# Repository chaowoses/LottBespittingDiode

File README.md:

# Lott-Bespitting Diode (LBD)

A high-intensity IR blaster built on the RP2040. Browser-native control over WebSerial, MOSFET-driven IR output, 38kHz NEC modulation. Fully open source.

[Home Page](https://chaowoses.dev/LottBespittingDiode/) &middot; [Controller](https://chaowoses.dev/LottBespittingDiode/controller.html)

Named for Mrs. Lott, the worst teacher I ever had, and her classroom projector.

---

## Features

- **Web Controller**: Full single-page app to manage IR remotes, browse the Flipper-IRDB, compose NEC signals, and transmit over WebSerial
- **In-Browser Schematic Viewer**: Browse all hardware schematics directly on the landing page via KiCanvas
- **Auto-Generated BOM**: Bill of materials extracted from KiCad schematics and embedded in the landing page, updated on every push
- **IRDB Integration**: Browse and import from [Lucaslhm/Flipper-IRDB](https://github.com/Lucaslhm/Flipper-IRDB) directly from the controller
- **NEC Protocol Engine**: CircuitPython firmware with hardware-timed 38kHz carrier modulation
- **Library Management**: Organize remotes and signals in folders with drag-and-drop, favorites, and inline editing

---

## Project Structure

```
app/                  # Web front-end
  index.html          # Landing page (hero, BOM, schematic viewer, docs)
  controller.html     # WebSerial controller app
  landing/
    index.css         # Landing page styles (dark theme, purple/amber)
    index.js          # Landing page interactivity (tabs, viewer)
    insults.json      # Footer quotes
    three-scene.js    # Three.js particle background
  controller/
    style.css         # Controller styles
    scripts/
      app.js          # Init, event listeners, tab switching
      state.js        # State management, library CRUD, localStorage
      serial.js       # WebSerial connection, log bar
      transmit.js     # Hex input, NEC encoding, transmit history, save form
      library-ui.js   # Library pane, remote view, favorites, inline edits
      sidebar.js      # Sidebar toggle, resize, tree rendering
      modals.js       # Modal dialogs (folder, rename, delete, clear)
      drag-drop.js    # Drag-and-drop reordering in sidebar tree
      import.js       # .ir file parsing and import
      irdb.js         # Flipper-IRDB browsing and import
      utils.js        # escHtml, escAttr helpers

firmware/             # CircuitPython firmware
  code.py             # NEC protocol engine over USB serial
  lib/                # Runtime libraries

hardware/             # KiCad hardware design
  LBD.kicad_sch       # Main schematic (RP2040, MOSFET, IR matrix)
  power.kicad_sch     # Power regulation (TPSM828214SILR)
  flash.kicad_sch     # External flash (W25Q128)
  usb.kicad_sch       # USB-C (USB4155)
  infared.kicad_sch   # IR LED output stage
  LBD.kicad_pcb       # PCB layout
  LBD_Library/        # Custom KiCad symbols and footprints
  prototype/          # Breadboard/perfboard prototype variant
  reviews/            # Design reviews and schematic analysis outputs

scripts/              # Utility scripts
  generate_bom.py     # Auto-generates BOM HTML from KiCad schematics
  ir_tester.py        # Standalone IR transmission test
```

---

## Hardware

> The embedded PCB design isn't finalized yet. Build the prototype on a breadboard or perfboard using the [prototype schematic](hardware/prototype.kicad_sch).

The full design targets a custom PCB with an RP2040, MOSFET-switched IR LED array, USB-C, and external flash. Five KiCad schematics cover the main board, power regulation, flash memory, USB connector, and a simplified prototype variant.

---

## Firmware

The [CircuitPython firmware](firmware/code.py) implements a standard NEC protocol engine:

- 38kHz carrier modulation via `pulseio.PulseOut`
- Listens for 4-byte NEC arrays over USB serial
- Drives a status LED and the IR output on GPIO
- Header: 9000&micro;s mark / 4500&micro;s space
- Bit coding: 560&micro;s mark + 1690&micro;s (1) or 560&micro;s (0)
- Compatible with any NEC IR receiver

```python
import time
import board
import pwmio

# 38kHz carrier wave initialization
ir_pwm = pwmio.PWMOut(board.GP16, frequency=38000, duty_cycle=0)

def pulse_nec(mark_us, space_us):
    # Enable carrier wave modulation for duration of mark
    ir_pwm.duty_cycle = 32768  # 50% duty cycle
    time.sleep_us(mark_us)

    # Disable carrier wave modulation for duration of space
    ir_pwm.duty_cycle = 0
    time.sleep_us(space_us)
```

---

## Web Interface

Two pages are served via GitHub Pages:

| Page | Description |
|---|---|
| **Landing Page** (`index.html`) | Project overview, BOM table, KiCanvas schematic viewer, architecture docs, features, setup guide |
| **Controller** (`controller.html`) | Full WebSerial-based remote control app with library management, IRDB browser, signal composer, and transmit history |

---

## Setup & Flash

> Build the prototype on a breadboard or perfboard using the [prototype schematic](hardware/prototype.kicad_sch).

<details>
<summary><strong>DIY / Prototype Only</strong>: Steps 1 and 2 (skip if you have a pre-assembled unit)</summary>

### Step 1: Enter Bootloader Mode

Press and hold the **BOOT** button on the board, then connect it to your computer via a data-capable USB cable. Release the button once the drive mounts.

### Step 2: Install CircuitPython

A mass storage volume named `RPI-RP2` will appear. Drag and drop the appropriate CircuitPython `.uf2` payload onto its root directory. The board will automatically reboot and remount as `CIRCUITPY`.

</details>

### Step 3: Deploy Firmware

Copy the contents of `firmware/` onto the `CIRCUITPY` volume root:

- `code.py`
- `lib/`

### Step 4: Plug It In & Open the Controller

Keep the device connected via USB, then open the [web controller](https://chaowoses.dev/LottBespittingDiode/controller.html) in a Chromium-based browser. Click **Connect** to establish the WebSerial session.

To run locally (required for development):

```bash
git clone https://github.com/chaowoses/LottBespittingDiode.git
cd LottBespittingDiode
python -m http.server 8080
# open http://localhost:8080
```

---

## License & Terms of Use

> [!CAUTION]
> **STRICTLY PROHIBITED FOR ILLEGAL USE**
>
> This project is designed solely for personal engineering research, hardware prototyping, and authorized testing.
> You may only operate this device on equipment you personally own or have explicit permission to control.
> The creator assumes no liability for misuse, property disruption, or equipment damage.

This project (software, firmware, schematics, PCB layouts, and documentation) is licensed under the **GNU General Public License v3.0 (GPL-3.0)**.

Copyright &copy; 2026 Josh Felder (Chaos). All Rights Reserved.

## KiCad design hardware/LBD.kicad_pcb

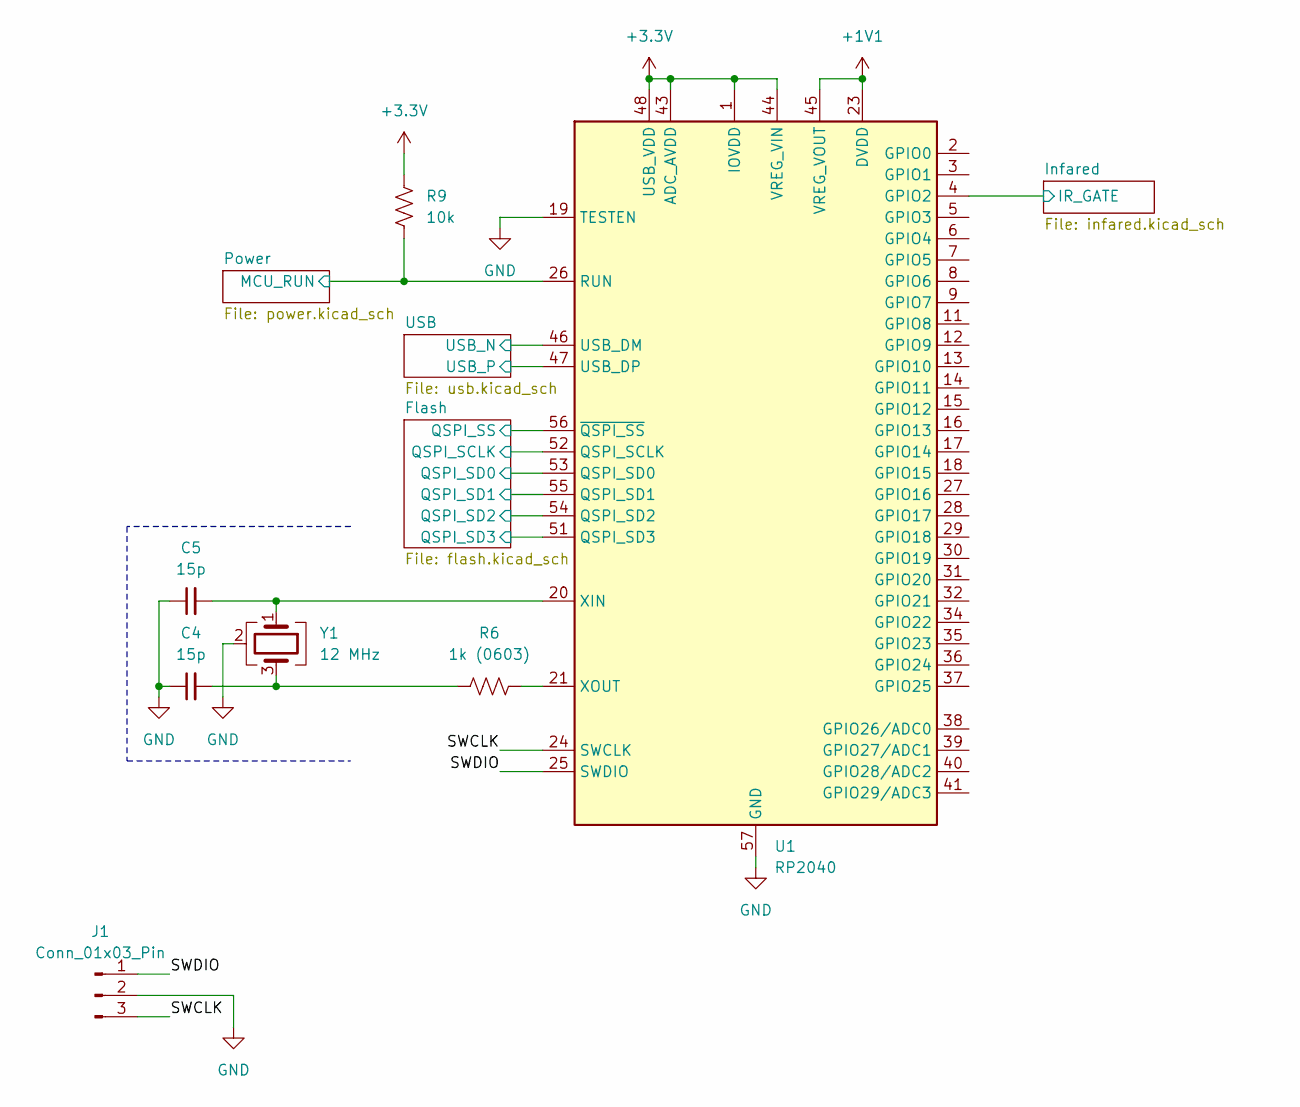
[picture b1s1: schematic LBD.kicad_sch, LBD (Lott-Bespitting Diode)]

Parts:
C4, C5: 15p; C_0201_0603Metric
J1: Conn_01x03_Pin; PinHeader_1x03_P2.54mm_Vertical_SMD_Pin1Left
R6: 1k (0603); R_0603_1608Metric
R9: 10k; R_0201_0603Metric
U1: RP2040; QFN-56-1EP_7x7mm_P0.4mm_EP3.2x3.2mm
Y1: 12 MHz

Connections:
+1V1: U1.23 (DVDD), U1.45 (VREG_VOUT), U1.50 (DVDD); also elsewhere on the board
+3.3V: R9.2, U1.1 (IOVDD), U1.10 (IOVDD), U1.22 (IOVDD), U1.33 (IOVDD), U1.42 (IOVDD), U1.43 (ADC_AVDD), U1.44 (VREG_VIN), U1.48 (USB_VDD), U1.49 (IOVDD); also elsewhere on the board
/Flash/QSPI_SCLK: U1.52 (QSPI_SCLK); also elsewhere on the board
/Flash/QSPI_SD0: U1.53 (QSPI_SD0); also elsewhere on the board
/Flash/QSPI_SD1: U1.55 (QSPI_SD1); also elsewhere on the board
/Flash/QSPI_SD2: U1.54 (QSPI_SD2); also elsewhere on the board
/Flash/QSPI_SD3: U1.51 (QSPI_SD3); also elsewhere on the board
/Flash/QSPI_SS: U1.56 (~QSPI_SS); also elsewhere on the board
/Infared/IR_GATE: U1.4 (GPIO2); also elsewhere on the board
/Power/PG: R9.1, U1.26 (RUN); also elsewhere on the board
/SWCLK: J1.3, U1.24 (SWCLK)
/SWDIO: J1.1, U1.25 (SWDIO)
/USB/USB_N: U1.46 (USB_DM); also elsewhere on the board
/USB/USB_P: U1.47 (USB_DP); also elsewhere on the board
GND: C4.1, C5.1, J1.2, U1.19 (TESTEN), U1.57 (GND), Y1.2 (G), Y1.4 (G); also elsewhere on the board
unnamed: C4.2, R6.2, Y1.3
unnamed: C5.2, U1.20 (XIN), Y1.1
unnamed: R6.1, U1.21 (XOUT)

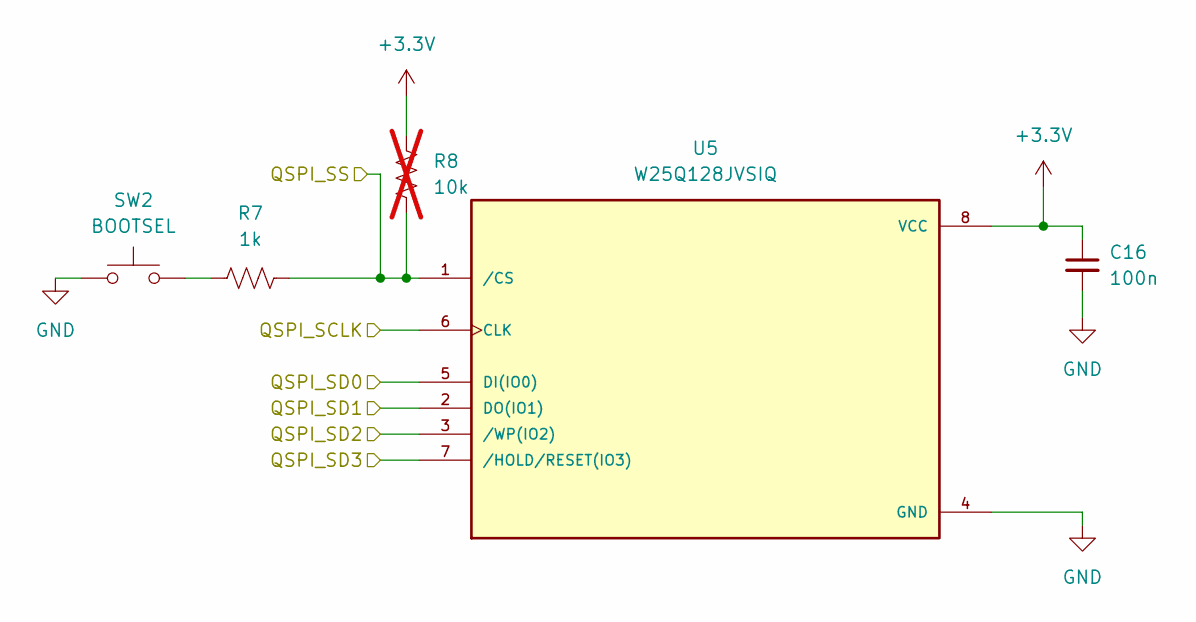
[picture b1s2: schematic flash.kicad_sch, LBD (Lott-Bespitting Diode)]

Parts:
C16: 100n; C_0201_0603Metric
R7: 1k; R_0201_0603Metric
R8: 10k; R_0201_0603Metric; not fitted
SW2: BOOTSEL; SW_SPST_B3U-1000P
U5: W25Q128JVSIQ; SOIC127P790X216-8N; PARTREV I

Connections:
+3.3V: C16.1, R8.2, U5.8 (VCC); also elsewhere on the board
/Flash/QSPI_SCLK: U5.6 (CLK); also elsewhere on the board
/Flash/QSPI_SD0: U5.5 (DI(IO0)); also elsewhere on the board
/Flash/QSPI_SD1: U5.2 (DO(IO1)); also elsewhere on the board
/Flash/QSPI_SD2: U5.3 (/WP(IO2)); also elsewhere on the board
/Flash/QSPI_SD3: U5.7 (/HOLD/RESET(IO3)); also elsewhere on the board
/Flash/QSPI_SS: R7.1, R8.1, U5.1 (/CS); also elsewhere on the board
GND: C16.2, SW2.1, U5.4 (GND); also elsewhere on the board
unnamed: R7.2, SW2.2

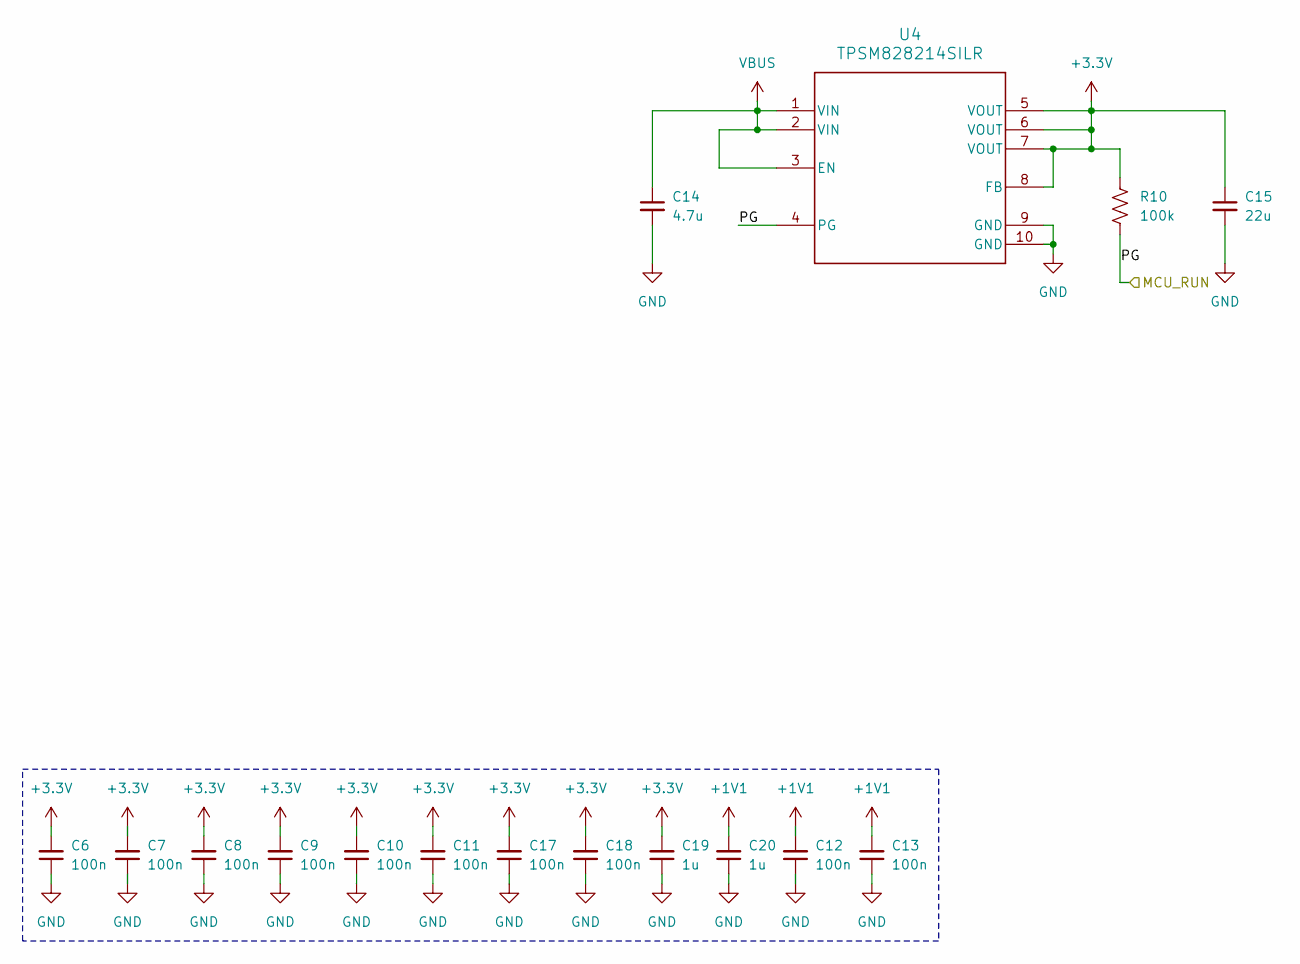
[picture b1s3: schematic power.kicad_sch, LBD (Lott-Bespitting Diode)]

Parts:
C6, C7, C8, C9, C10, C11, C12, C13, C17, C18: 100n; C_0201_0603Metric
C14: 4.7u; C_0603_1608Metric
C15: 22u; C_0603_1608Metric
C19, C20: 1u; C_0402_1005Metric
R10: 100k; R_0201_0603Metric
U4: TPSM828214SILR

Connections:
+1V1: C12.2, C13.2, C20.2; also elsewhere on the board
+3.3V: C6.2, C7.2, C8.2, C9.2, C10.2, C11.2, C15.1, C17.2, C18.2, C19.2, R10.2, U4.5 (VOUT), U4.6 (VOUT), U4.7 (VOUT), U4.8 (FB); also elsewhere on the board
/Power/PG: R10.1, U4.4 (PG); also elsewhere on the board
GND: C6.1, C7.1, C8.1, C9.1, C10.1, C11.1, C12.1, C13.1, C14.2, C15.2, C17.1, C18.1, C19.1, C20.1, U4.9 (GND), U4.10 (GND); also elsewhere on the board
VBUS: C14.1, U4.1 (VIN), U4.2 (VIN), U4.3 (EN); also elsewhere on the board

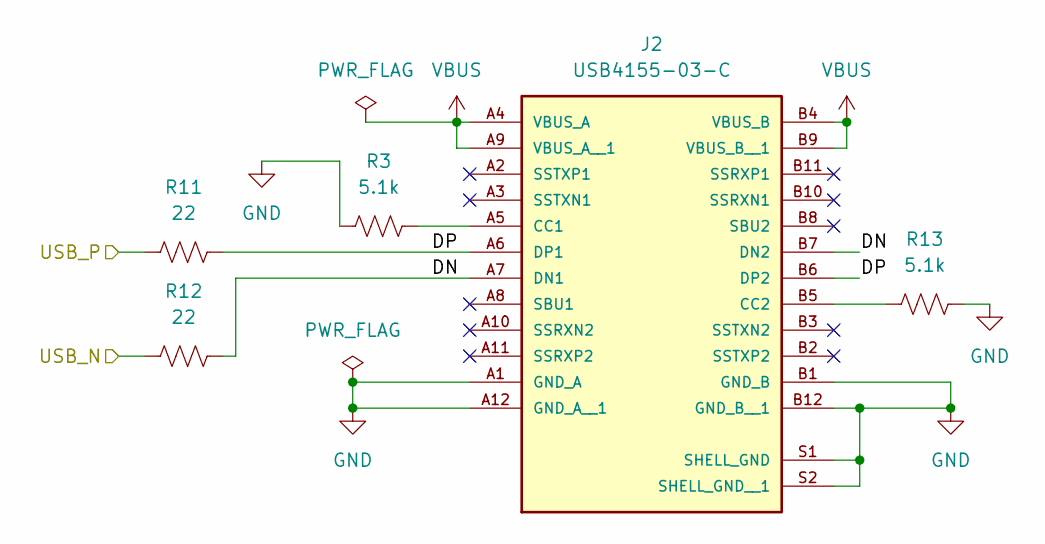
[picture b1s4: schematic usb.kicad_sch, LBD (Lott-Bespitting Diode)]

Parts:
J2: USB4155-03-C; GCT_USB4155-03-C_REVA; PARTREV A
R3, R13: 5.1k; R_0201_0603Metric
R11, R12: 22; R_0201_0603Metric

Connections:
/USB/DN: J2.A7 (DN1), J2.B7 (DN2), R12.2
/USB/DP: J2.A6 (DP1), J2.B6 (DP2), R11.2
/USB/USB_N: R12.1; also elsewhere on the board
/USB/USB_P: R11.1; also elsewhere on the board
GND: J2.A1 (GND_A), J2.A12 (GND_A__1), J2.B1 (GND_B), J2.B12 (GND_B__1), J2.S1 (SHELL_GND), J2.S2 (SHELL_GND__1), R3.1, R13.2; also elsewhere on the board
unnamed: J2.A5 (CC1), R3.2
unnamed: J2.B5 (CC2), R13.1
VBUS: J2.A4 (VBUS_A), J2.A9 (VBUS_A__1), J2.B4 (VBUS_B), J2.B9 (VBUS_B__1); also elsewhere on the board

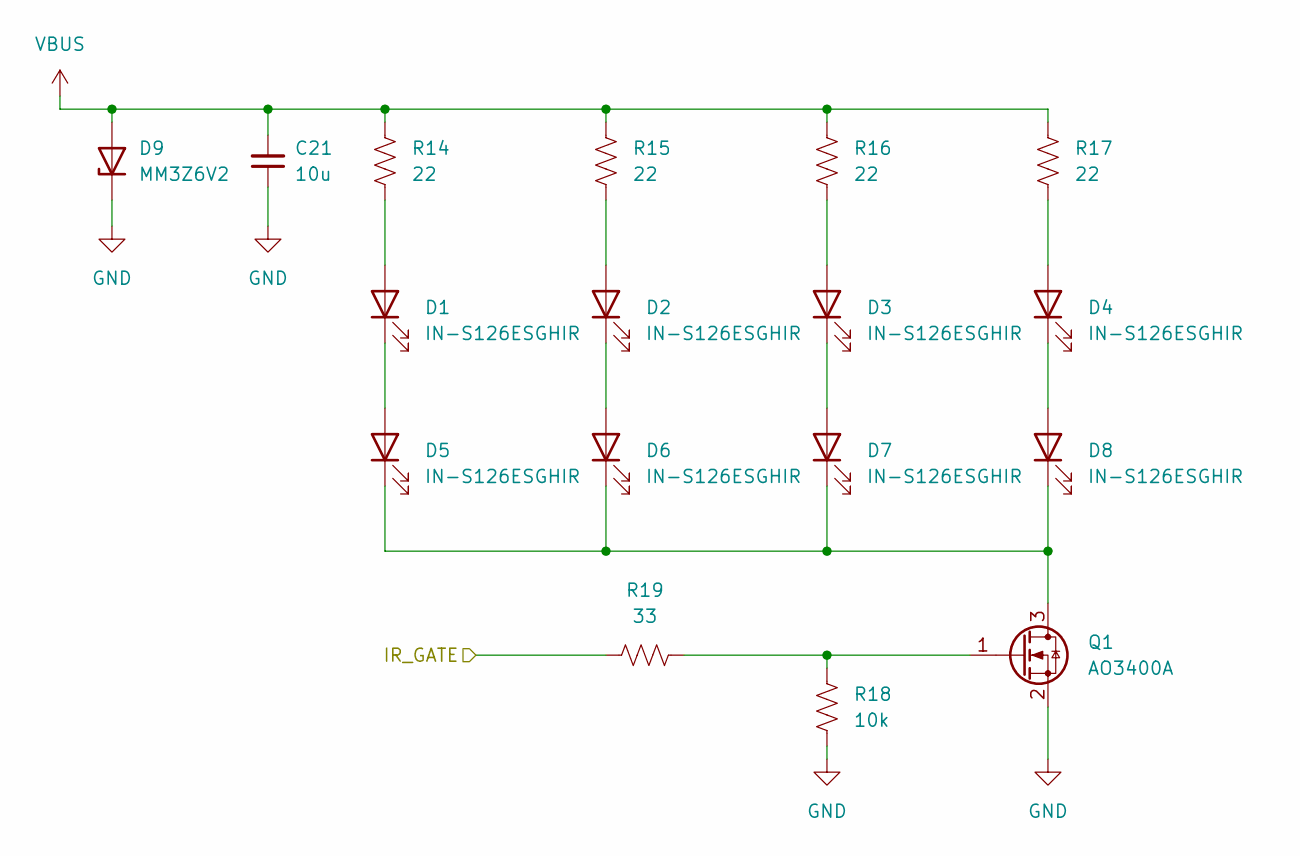
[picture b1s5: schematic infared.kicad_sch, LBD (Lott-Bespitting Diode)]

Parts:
C21: 10u; C_0603_1608Metric
D1, D2, D3, D4, D5, D6, D7, D8: IN-S126ESGHIR; LED_IN-S12_INL
D9: MM3Z6V2; D_SOD-323
Q1: AO3400A; SOT-23
R14, R15, R16, R17: 22; R_0603_1608Metric
R18: 10k; R_0201_0603Metric
R19: 33; R_0603_1608Metric

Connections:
/Infared/IR_GATE: R19.2; also elsewhere on the board
GND: C21.1, D9.1 (K), Q1.2 (S), R18.1; also elsewhere on the board
unnamed: D1.2 (A), R14.1
unnamed: D1.1 (K), D5.2 (A)
unnamed: D2.2 (A), R15.1
unnamed: D2.1 (K), D6.2 (A)
unnamed: D3.2 (A), R16.1
unnamed: D3.1 (K), D7.2 (A)
unnamed: D4.2 (A), R17.1
unnamed: D4.1 (K), D8.2 (A)
unnamed: D5.1 (K), D6.1 (K), D7.1 (K), D8.1 (K), Q1.3 (D)
unnamed: Q1.1 (G), R18.2, R19.1
VBUS: C21.2, D9.2 (A), R14.2, R15.2, R16.2, R17.2; also elsewhere on the board

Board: 4 copper layers, 50 parts (0 on the bottom side), 34 nets, no tracks yet.

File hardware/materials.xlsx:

Description | Manufacturer | Manufacturer Part Number | Digikey Part Number | Link | Quantity | Libraries | Datasheet
ARM® Cortex®-M0+ - Microcontroller IC 32-Bit Dual-Core 133MHz External Program 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 | Raspberry Pi | SC0914(13) | 2648-SC0914(13)CT-ND | https://www.digikey.com/en/products/detail/raspberry-pi/SC09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 | 1 | https://www.digikey.com/en/models/14306010 | https://datasheets.raspberrypi.com/rp2040/rp2040-datasheet.pdf
USB-C (USB TYPE-C) USB 3.2 Gen 2 (USB 3.1 Gen 2, Superspeed + (USB 3.1)) Plug C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 | GCT | USB4155-03-C | 2073-USB4155-03-CCT-ND | https://www.digikey.com/en/products/detail/gct/USB4155-03-C/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 | 1 | https://www.digikey.com/en/models/14305161?tab=snapmagic | https://gct.co/files/specs/usb4155-spec.pdf
Infrared (IR) Emitter 940nm 1.46V 100mA 92mW/sr @ 100mA (Typ) 30° 1210 (3225 Me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 | Inolux | IN-S126ESGHIR | 1830-IN-S126ESGHIRCT-ND | https://www.digikey.com/en/products/detail/inolux/IN-S126ESG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 | 8 | https://www.digikey.com/en/models/10384762?tab=ultralibrarian | http://www.inolux-corp.com/datasheet/IR/Emitter/940%20nm%20S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
N-Channel 30 V 5.7A (Ta) 1.4W (Ta) Surface Mount SOT-23-3 | Alpha & Omega Semiconductor Inc. | AO3400A | 785-1000-1-ND | https://www.digikey.com/en/products/detail/alpha-omega-semic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 | 1 | https://www.digikey.com/en/models/1855772?tab=snapmagic | https://mm.digikey.com/Volume0/opasdata/d220001/medias/docus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
Non-Isolated PoL Module DC DC Converter 1 Output 3.3V 1A 2.4V - 5.5V Input | Texas Instruments | TPSM828214SILR | 296-TPSM828214SILRCT-ND | https://www.digikey.com/en/products/detail/texas-instruments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 | 1 | https://www.digikey.com/en/models/14124001?tab=ultralibrarian | https://www.ti.com/lit/ds/symlink/tpsm82821.pdf?HQS=dis-dk-n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
FLASH - NOR Memory IC 128Mbit SPI - Quad I/O, QPI 133 MHz 8-SOIC | Winbond Electronics | W25Q128JVSIQ | W25Q128JVSIQ-ND | https://www.digikey.com/en/products/detail/winbond-electroni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 | 1 | https://www.digikey.com/en/models/5803943 | https://mm.digikey.com/Volume0/opasdata/d220001/medias/docus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
12 MHz ±30ppm Crystal 10pF 50 Ohms 4-SMD, No Lead | Abracon LLC | ABM8-272-T3 | 535-ABM8-272-T3CT-ND | https://www.digikey.com/en/products/detail/abracon-llc/ABM8-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 | 1 | https://www.digikey.com/en/models/22472366?tab=ultralibrarian | https://abracon.com/datasheets/ABM8-272-T3.pdf
Tactile Switch SPST-NO Top Actuated Surface Mount | Aratas America LLC | B3U-1000P | SW1020CT-ND | https://www.digikey.com/en/products/detail/omron-electronics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 | 1 | https://www.digikey.com/en/models/1534338 | https://omronfs.omron.com/en_US/ecb/products/pdf/en-b3u.pdf

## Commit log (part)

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2026-05-14 created symbol and footprint libraries
2026-05-23 chore: untrack and ignore .vscode folder
2026-05-23 gitignore
2026-05-23 readme, license
2026-05-23 license
2026-05-28 i forgot what i changed
2026-05-28 oh i remember what i did i created random files for some reason also made hierarchical labels
2026-05-28 changed global labels to hierarchical labels
2026-05-28 switched back to globals
2026-05-29 cleaned up repo structure
2026-05-29 fixed wiring errors
2026-06-01 fixed permissions
2026-06-02 added pages instruction to readme
2026-06-02 swapped order
2026-06-02 redid frontend to match theme
2026-06-02 recolored stuff
2026-06-02 added insults towards mrs lott and allen
2026-06-06 improved website graphics
2026-06-06 allowed schematic files to display on gh pages
2026-06-06 reorganized ui
2026-06-06 added bom generator
2026-06-06 made bom update in main
2026-06-06 Update BOM from schematics [skip ci]
2026-06-06 added links in readme
2026-06-06 removed favicon
2026-06-06 changed gh username
2026-06-13 moved insults towards mrs lott and allen to a json file so that allen can read them easier and cry
2026-06-23 cleaned codebase to run on slightly more attainable hopes and dreams
2026-06-23 refactor: update display value from LED to IN-S126ESGHIR
2026-06-23 style: improve aesthetics of placeholder PCB 3D display
2026-06-23 chore: stop local BOM updates on commit
    Updated the build script to prevent the BOM on the website from updating locally during commit.
2026-06-23 docs: create agents documentation
2026-06-23 docs: create CLAUDE.md
2026-06-23 style: redesigned PCB 3D
2026-06-25 resositioned leds
2026-06-26 chore: ignore generated markdown documentation
2026-06-26 docs: add datasheet for AO3400A N-Channel MOSFET
2026-06-26 feat: implement IR matrix
2026-06-26 feat: added git history display
2026-06-26 build: update bom for website
2026-06-26 fix: render prototype on website schematic viewer
2026-06-27 docs(sheet): update title of schematic sheets
2026-06-27 fix: fix mobile ui not spanning entire width
2026-06-27 deploy: 185cbaaa445767577eda45ccdfecd190ea889b4a
2026-06-29 docs: add datasheets
    Add datasheets for Voltage Regulator, USB-C connector, Flash, TVS Diode, and RP2040
2026-06-29 fix: remove REV_A suffix from schematic symbol
2026-06-29 feat: add design review documentation
2026-06-29 docs: update repository structure in readme
2026-06-29 docs: add design review info
